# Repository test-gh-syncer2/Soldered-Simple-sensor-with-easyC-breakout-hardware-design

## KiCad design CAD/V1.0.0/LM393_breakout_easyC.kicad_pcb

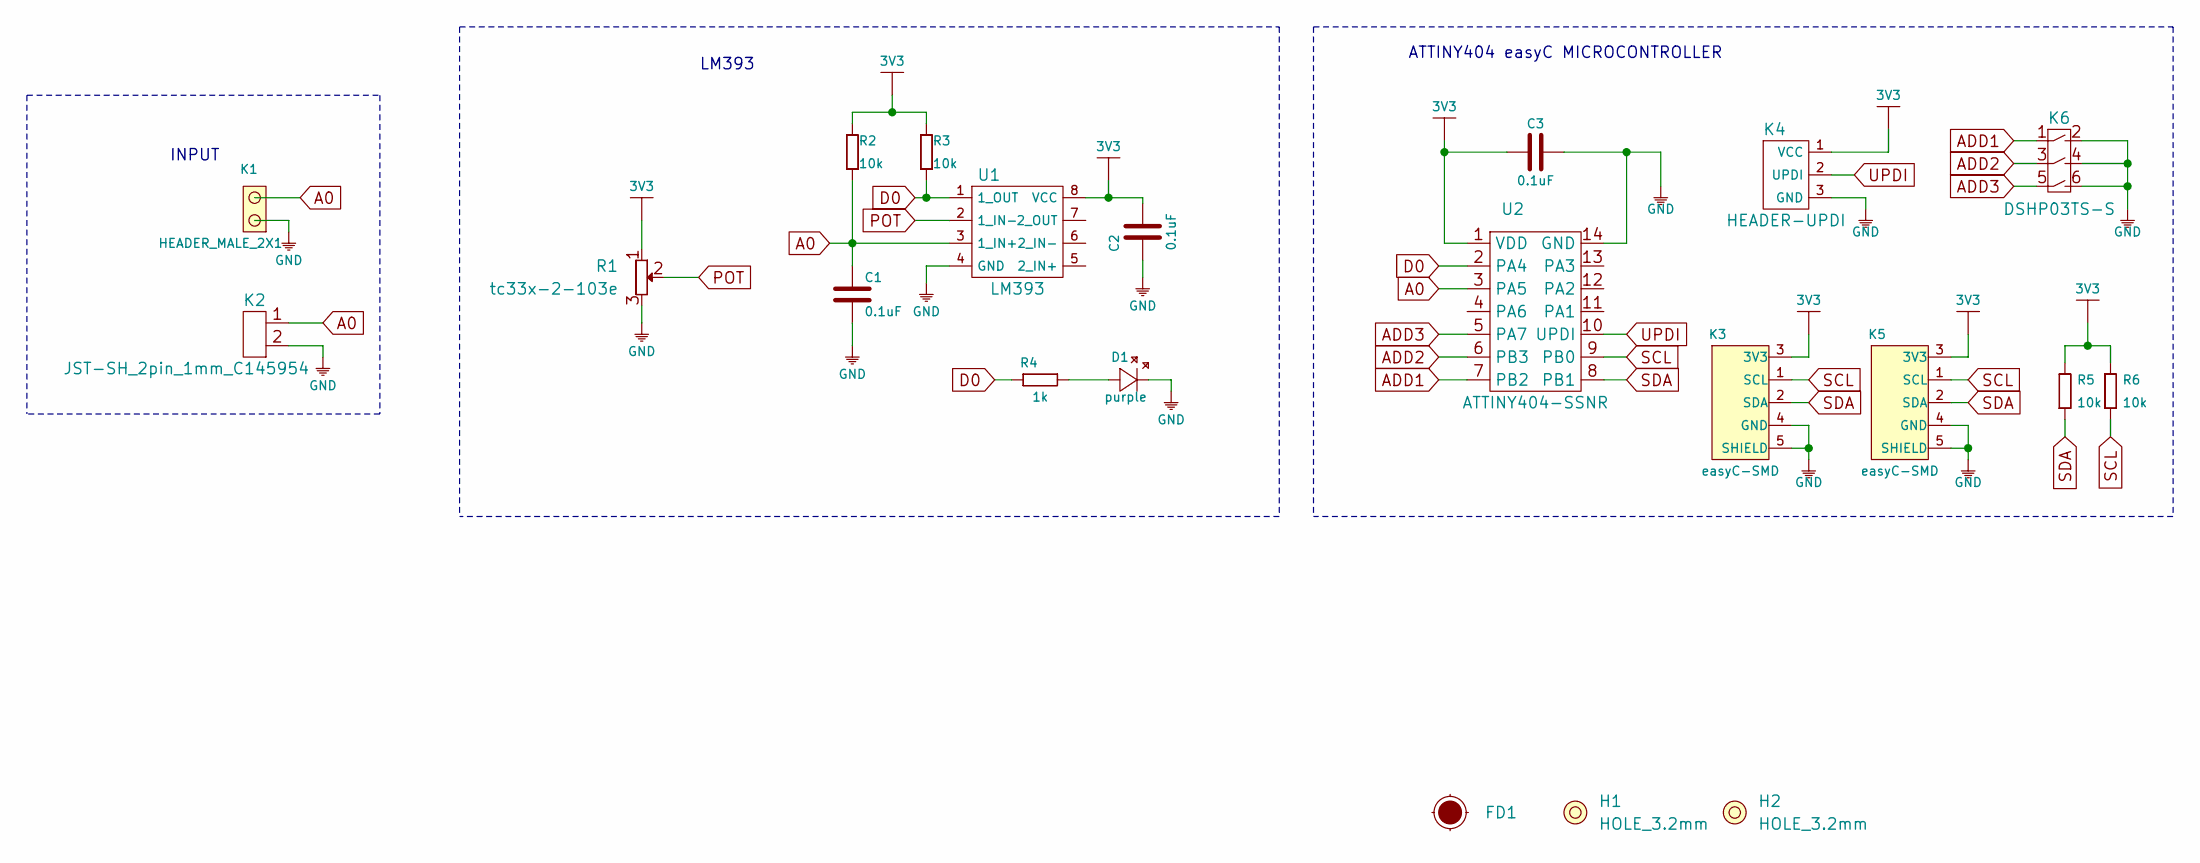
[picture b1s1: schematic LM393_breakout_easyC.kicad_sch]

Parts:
C1, C2, C3: 0.1uF; 0603C
D1: purple; 0402LED
FD1: Fiducial_Stencil; FIDUCIAL_1MM_PASTE
H1, H2: HOLE_3.2mm
K1: HEADER_MALE_2X1
K2: JST-SH_2pin_1mm_C145954
K3, K5: easyC-SMD; easyC-connector
K4: HEADER-UPDI
K6: DSHP03TS-S
R1: tc33x-2-103e
R2, R3, R5, R6: 10k; 0603R
R4: 1k; 0402R
U1: LM393; SOIC−8
U2: ATTINY404-SSNR; SOIC-14

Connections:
3V3: C2.2, C3.1, K3.3 (3V3), K4.1 (VCC), K5.3 (3V3), R1.1, R2.2, R3.2, R5.2, R6.2, U1.8 (VCC), U2.1 (VDD)
A0: C1.2, K1.2, K2.1, R2.1, U1.3 (1_IN+), U2.3 (PA5)
ADD1: K6.1, U2.7 (PB2)
ADD2: K6.3, U2.6 (PB3)
ADD3: K6.5, U2.5 (PA7)
D0: R3.1, R4.1, U1.1 (1_OUT), U2.2 (PA4)
GND: C1.1, C2.1, C3.2, D1.2 (K), K1.1, K2.2, K3.4 (GND), K3.5 (SHIELD), K4.3 (GND), K5.4 (GND), K5.5 (SHIELD), K6.2, K6.4, K6.6, R1.3, U1.4 (GND), U2.14 (GND)
unnamed: D1.1 (A), R4.2
POT: R1.2, U1.2 (1_IN-)
SCL: K3.1 (SCL), K5.1 (SCL), R6.1, U2.9 (PB0)
SDA: K3.2 (SDA), K5.2 (SDA), R5.1, U2.8 (PB1)
UPDI: K4.2 (UPDI), U2.10 (UPDI)

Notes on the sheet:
INPUT
LM393
ATTINY404 easyC MICROCONTROLLER

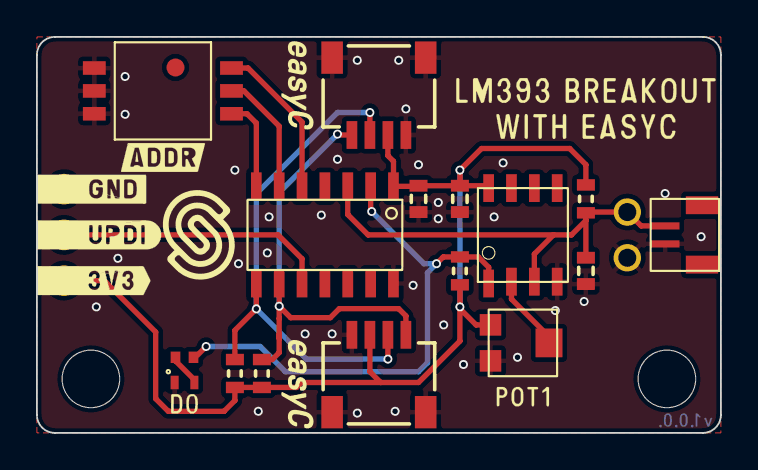
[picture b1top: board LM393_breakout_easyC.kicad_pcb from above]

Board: 2 copper layers, 38.0 x 22.0 mm, 21 parts (0 on the bottom side), 12 nets.

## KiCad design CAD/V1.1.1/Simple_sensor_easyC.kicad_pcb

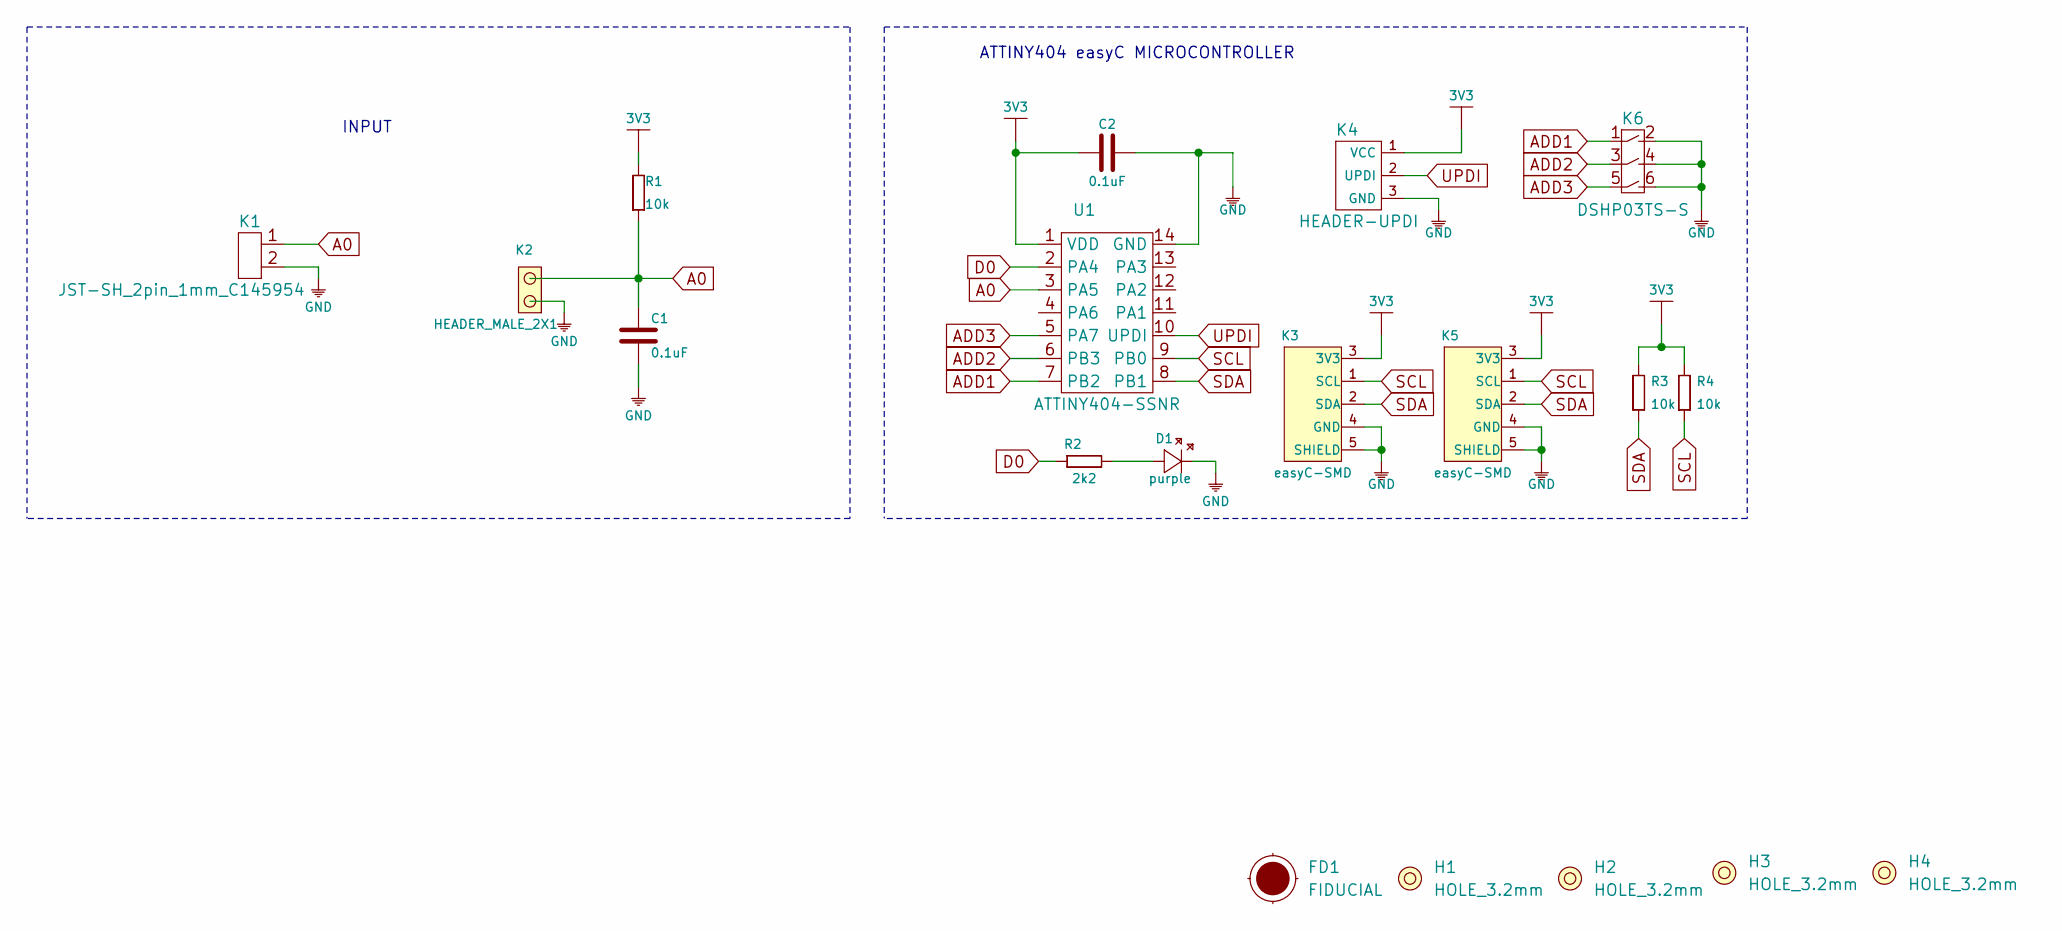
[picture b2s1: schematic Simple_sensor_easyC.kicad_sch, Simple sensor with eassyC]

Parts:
C1, C2: 0.1uF; 0603C
D1: purple; 0402LED
FD1: FIDUCIAL; FIDUCIAL_23
H1, H2, H3, H4: HOLE_3.2mm
K1: JST-SH_2pin_1mm_C145954
K2: HEADER_MALE_2X1
K3, K5: easyC-SMD; easyC-connector
K4: HEADER-UPDI
K6: DSHP03TS-S
R1, R3, R4: 10k; 0603R
R2: 2k2; 0402R
U1: ATTINY404-SSNR; SOIC-14

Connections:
3V3: C2.1, K3.3 (3V3), K4.1 (VCC), K5.3 (3V3), R1.2, R3.2, R4.2, U1.1 (VDD)
A0: C1.2, K1.1, K2.2, R1.1, U1.3 (PA5)
ADD1: K6.1, U1.7 (PB2)
ADD2: K6.3, U1.6 (PB3)
ADD3: K6.5, U1.5 (PA7)
D0: R2.1, U1.2 (PA4)
GND: C1.1, C2.2, D1.2 (K), K1.2, K2.1, K3.4 (GND), K3.5 (SHIELD), K4.3 (GND), K5.4 (GND), K5.5 (SHIELD), K6.2, K6.4, K6.6, U1.14 (GND)
unnamed: D1.1 (A), R2.2
SCL: K3.1 (SCL), K5.1 (SCL), R4.1, U1.9 (PB0)
SDA: K3.2 (SDA), K5.2 (SDA), R3.1, U1.8 (PB1)
UPDI: K4.2 (UPDI), U1.10 (UPDI)

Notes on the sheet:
INPUT
ATTINY404 easyC MICROCONTROLLER

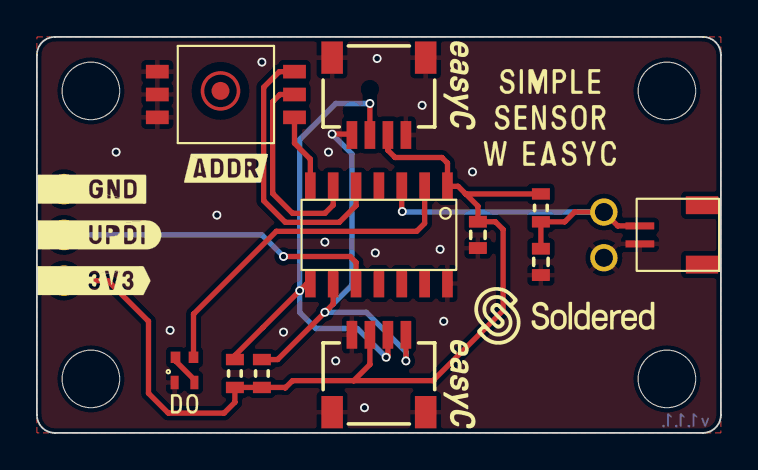
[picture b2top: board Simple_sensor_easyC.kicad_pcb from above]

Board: 2 copper layers, 38.0 x 22.0 mm, 19 parts (0 on the bottom side), 11 nets.

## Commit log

2021-09-23 Syncing to git
2021-09-23 Updating open source files.
